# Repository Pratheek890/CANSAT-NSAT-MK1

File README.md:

# CANSAT-NSAT-MK1
In accordance with the guidelines of IN-SPACe and the ASI CanSat competition, we designed and developed a rocket tailored for the mission requirements.,among few participants we have been selected for final launch at Kushinagar

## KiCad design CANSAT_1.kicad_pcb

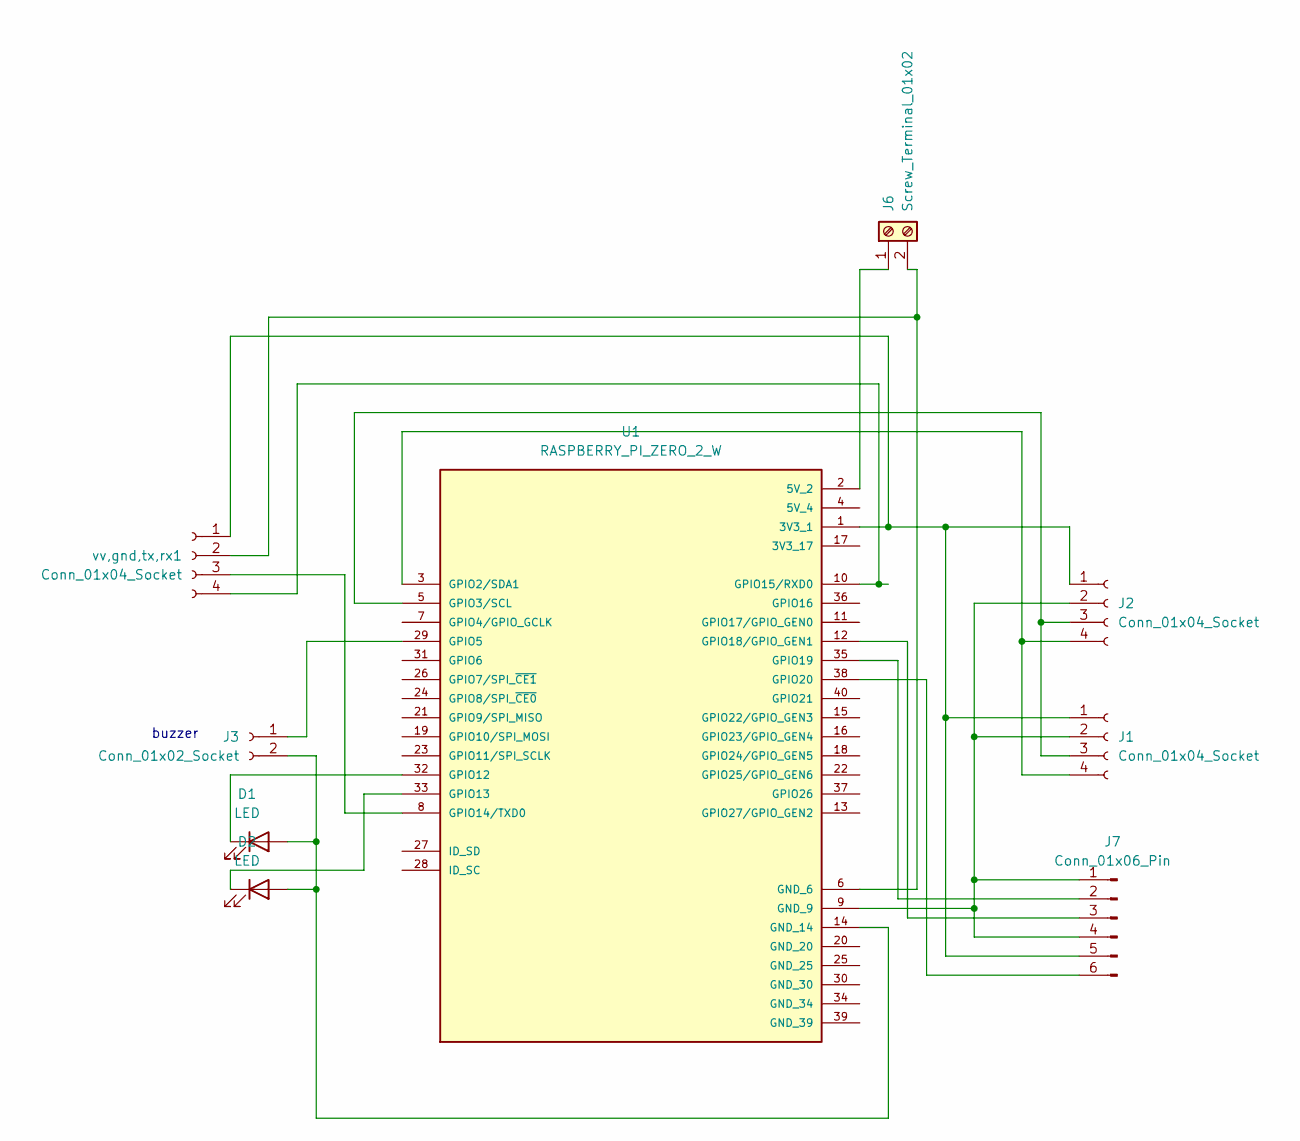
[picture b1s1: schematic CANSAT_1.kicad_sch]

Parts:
D1, D2: LED; LED_D2.0mm_W4.0mm_H2.8mm_FlatTop
J1, J2: Conn_01x04_Socket; NS-Tech_Grove_1x04_P2mm_Vertical
J3: Conn_01x02_Socket; PinSocket_1x02_P2.00mm_Vertical
J6: Screw_Terminal_01x02; TerminalBlock_Altech_AK300-2_P5.00mm
J7: Conn_01x06_Pin; through hole 3-3
U1: RASPBERRY_PI_ZERO_2_W; MODULE_RASPBERRY_PI_ZERO_2_W; PARTREV April 2024
vv,gnd,tx,rx1: Conn_01x04_Socket; NS-Tech_Grove_1x04_P2mm_Vertical

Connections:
unnamed: D1.2 (A), D2.2 (A), J3.2, U1.14 (GND_14)
unnamed: D1.1 (K), U1.32 (GPIO12)
unnamed: D2.1 (K), U1.33 (GPIO13)
unnamed: J1.1, J2.1, J7.5, U1.1 (3V3_1), vv,gnd,tx,rx1.1
unnamed: J1.2, J2.2, J7.1, J7.4, U1.9 (GND_9)
unnamed: J1.3, J2.3, U1.5 (GPIO3/SCL)
unnamed: J1.4, J2.4, U1.3 (GPIO2/SDA1)
unnamed: J3.1, U1.29 (GPIO5)
unnamed: J6.1, U1.2 (5V_2)
unnamed: J6.2, U1.6 (GND_6), vv,gnd,tx,rx1.2
unnamed: J7.2, U1.35 (GPIO19)
unnamed: J7.3, U1.12 (GPIO18/GPIO_GEN1)
unnamed: J7.6, U1.38 (GPIO20)
unnamed: U1.8 (GPIO14/TXD0), vv,gnd,tx,rx1.3
unnamed: U1.10 (GPIO15/RXD0), vv,gnd,tx,rx1.4

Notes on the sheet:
buzzer

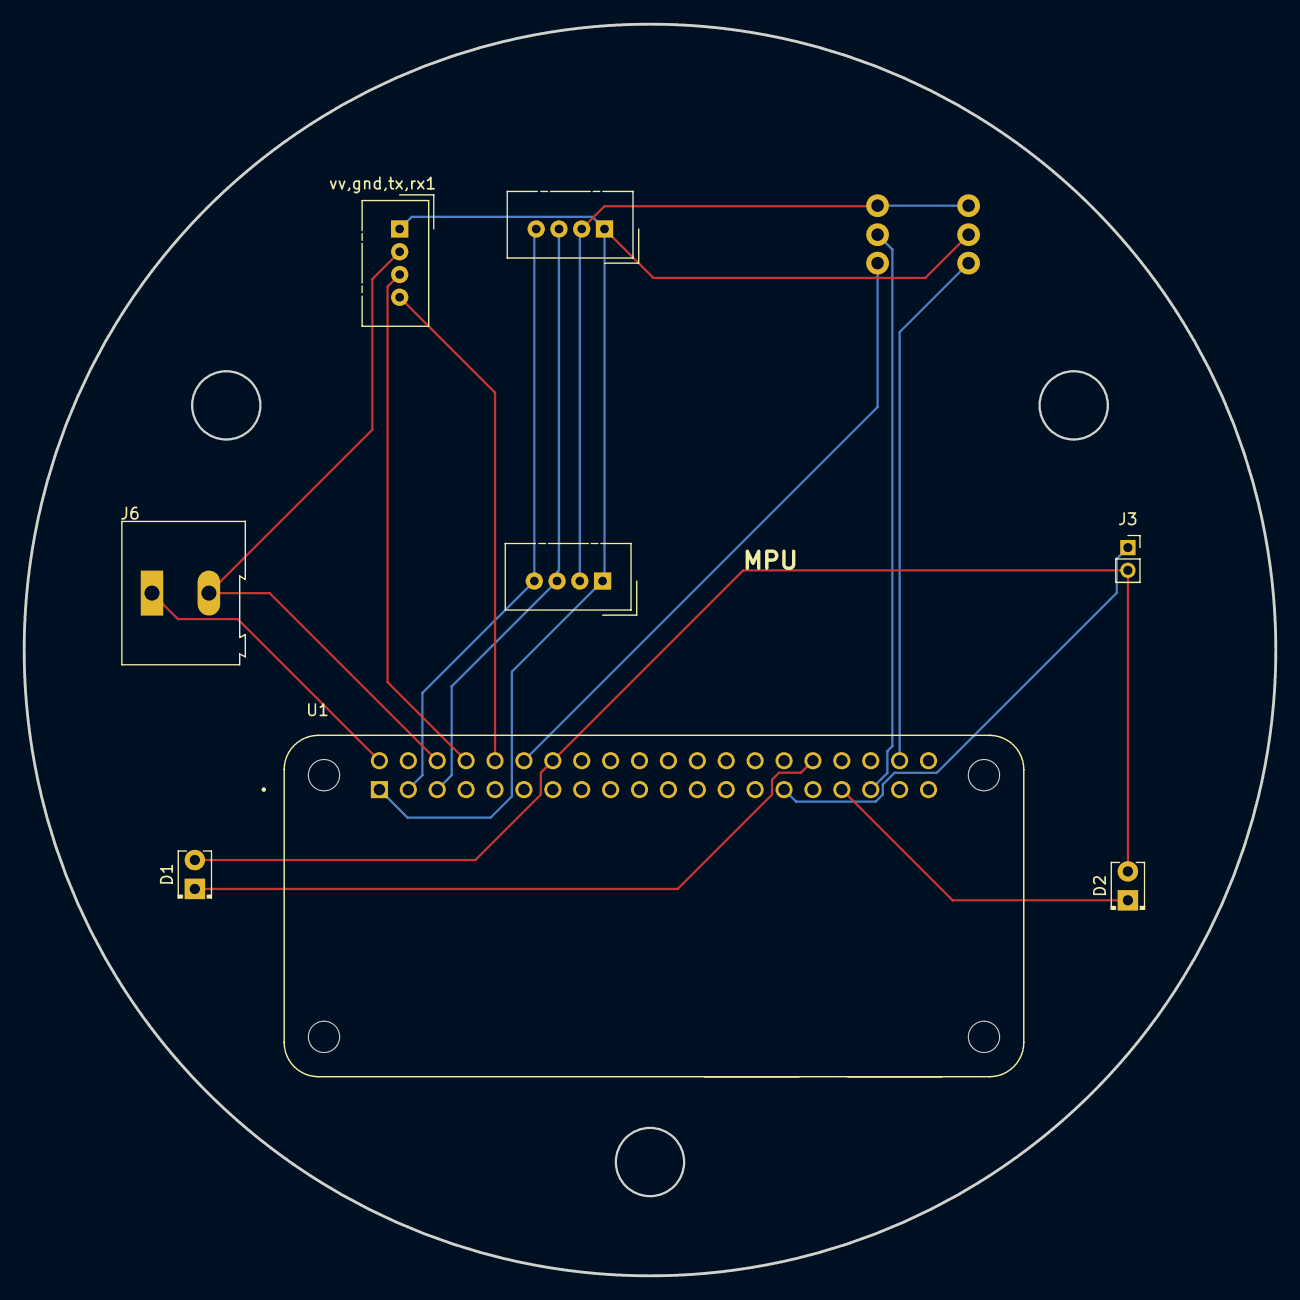
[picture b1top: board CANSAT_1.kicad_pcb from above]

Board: 2 copper layers, 110.0 x 110.0 mm, 9 parts (0 on the bottom side), 15 nets.

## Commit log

2025-09-05 INMP441 custom made footprint
2025-09-05 Schematic diagram of PCB layout
    this includes Raspberry Pi 2W , BME680 , MPU6050,0, 2 LEDs, 1 Pixhawk, and screw terminal (input power supply)
2025-09-05 PCB layout
2025-09-05 Gerber file for fabrication
2025-09-13 final folder
2025-09-13 final design
